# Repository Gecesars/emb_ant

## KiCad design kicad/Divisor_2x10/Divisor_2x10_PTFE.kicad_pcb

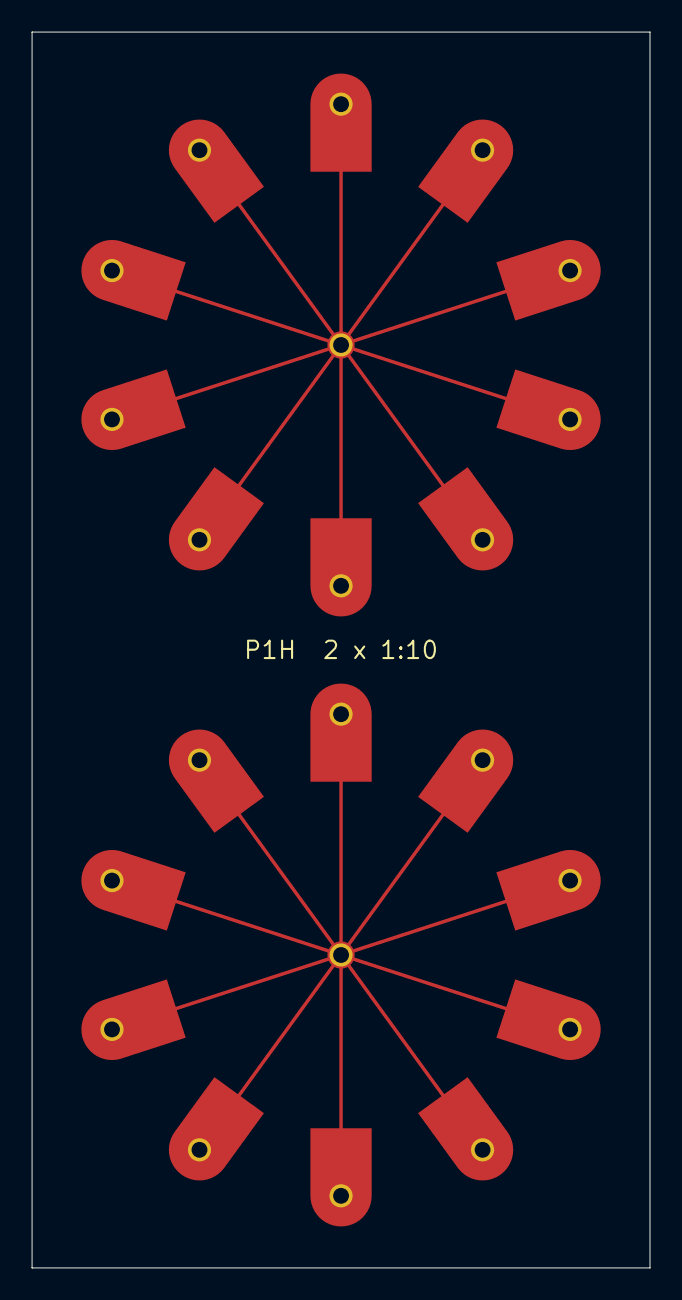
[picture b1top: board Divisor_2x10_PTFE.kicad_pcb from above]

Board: 2 copper layers, 39.0 x 78.0 mm, 22 parts (0 on the bottom side), 3 nets, no tracks yet.

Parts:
J1: A_IN_UT141C
J2: A1_UT141C
J3: A2_UT141C
J4: A3_UT141C
J5: A4_UT141C
J6: A5_UT141C
J7: A6_UT141C
J8: A7_UT141C
J9: A8_UT141C
J10: A9_UT141C
J11: A10_UT141C
J12: B_IN_UT141C
J13: B1_UT141C
J14: B2_UT141C
J15: B3_UT141C
J16: B4_UT141C
J17: B5_UT141C
J18: B6_UT141C
J19: B7_UT141C
J20: B8_UT141C
J21: B9_UT141C
J22: B10_UT141C

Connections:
GND: J1.2, J2.2, J3.2, J4.2, J5.2, J6.2, J7.2, J8.2, J9.2, J10.2, J11.2, J12.2, J13.2, J14.2, J15.2, J16.2, J17.2, J18.2, J19.2, J20.2, J21.2, J22.2
POL_A: J1.1, J2.1, J3.1, J4.1, J5.1, J6.1, J7.1, J8.1, J9.1, J10.1, J11.1
POL_B: J12.1, J13.1, J14.1, J15.1, J16.1, J17.1, J18.1, J19.1, J20.1, J21.1, J22.1

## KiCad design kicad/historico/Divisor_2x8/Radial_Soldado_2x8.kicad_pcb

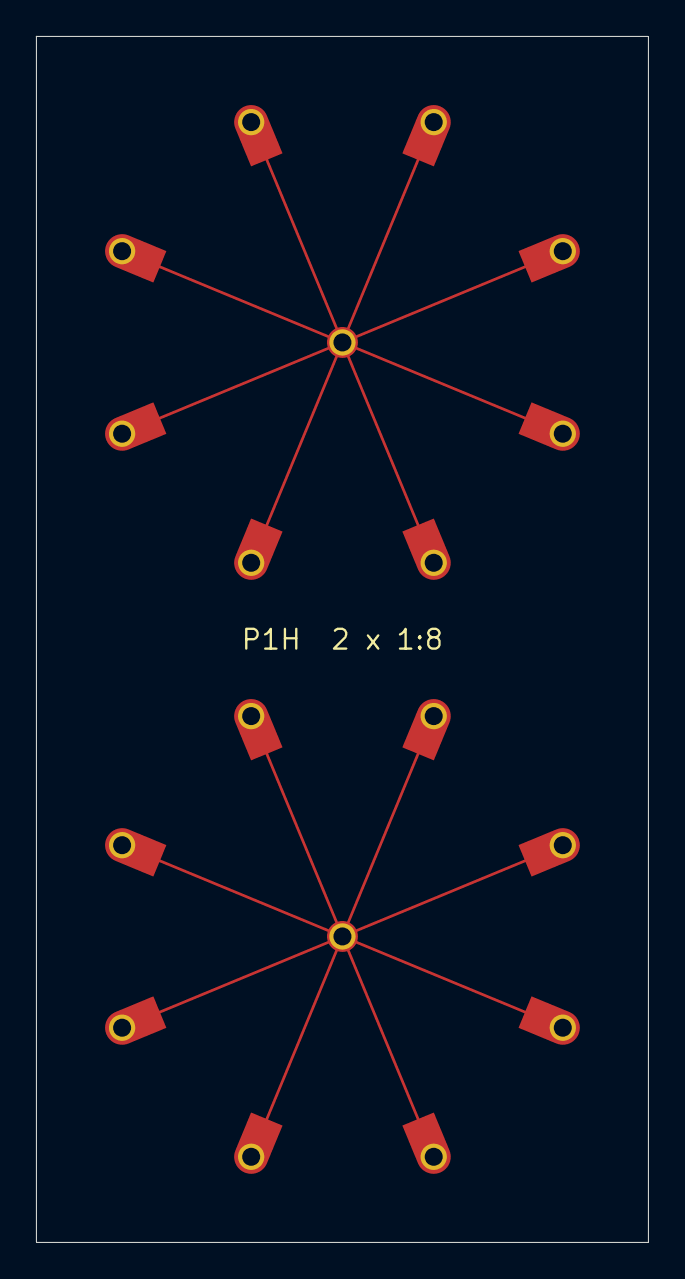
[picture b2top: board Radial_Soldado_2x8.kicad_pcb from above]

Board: 2 copper layers, 34.0 x 67.0 mm, 18 parts (0 on the bottom side), 3 nets, no tracks yet.

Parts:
J1: A_IN_UT141C
J2: A1_UT141C
J3: A2_UT141C
J4: A3_UT141C
J5: A4_UT141C
J6: A5_UT141C
J7: A6_UT141C
J8: A7_UT141C
J9: A8_UT141C
J10: B_IN_UT141C
J11: B1_UT141C
J12: B2_UT141C
J13: B3_UT141C
J14: B4_UT141C
J15: B5_UT141C
J16: B6_UT141C
J17: B7_UT141C
J18: B8_UT141C

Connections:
GND: J1.2, J2.2, J3.2, J4.2, J5.2, J6.2, J7.2, J8.2, J9.2, J10.2, J11.2, J12.2, J13.2, J14.2, J15.2, J16.2, J17.2, J18.2
POL_A: J1.1, J2.1, J3.1, J4.1, J5.1, J6.1, J7.1, J8.1, J9.1
POL_B: J10.1, J11.1, J12.1, J13.1, J14.1, J15.1, J16.1, J17.1, J18.1
